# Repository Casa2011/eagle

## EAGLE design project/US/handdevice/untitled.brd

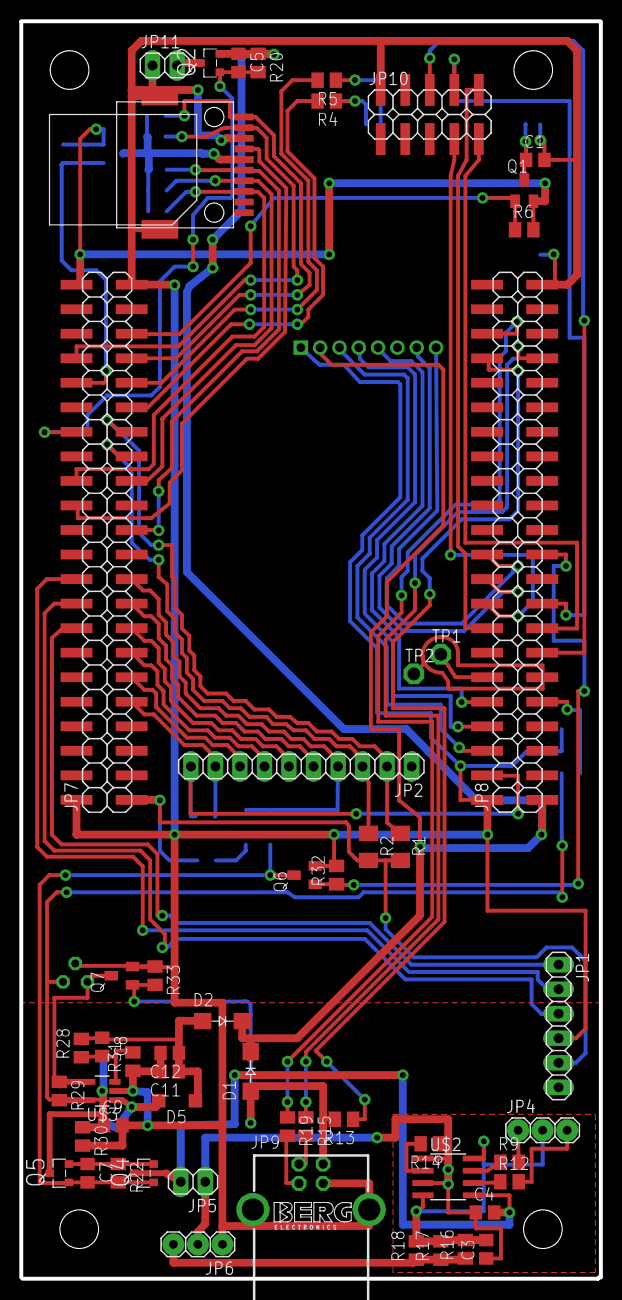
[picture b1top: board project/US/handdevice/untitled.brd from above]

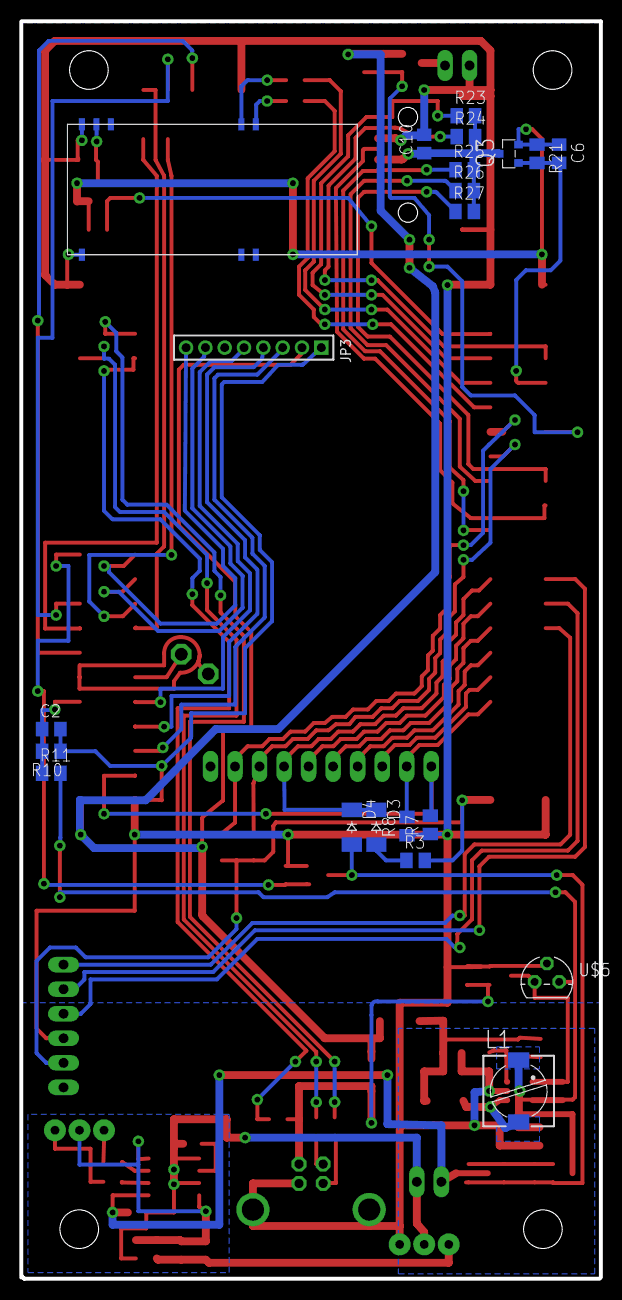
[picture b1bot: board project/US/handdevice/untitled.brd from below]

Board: 2 copper layers, 60.0 x 130.2 mm, 76 parts (21 on the bottom side), 68 nets.

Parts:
C1, C3, C9, C10, C11, C12: 10u; C0805
C2, C5, C6, C7: 100n; C0805
C4: 1u; C0805
C8: 200p; C0805
D1, D2: SS16; SMA-DO214AC
D3, D4: 1n4007; SOD-123_MINI-SMA
D5: SS14; SOD123
JP1: realtime_clock; 1X06
JP2: keyboard; 1X10
JP3: amplifier_control; 1X08M
JP4: charge_slot; 1X03
JP5: battery; 1X02
JP6: chrg; 1X03
JP7: left_cpu; 2X22SMD
JP8: right_cpu; 2X22SMD
JP9: USB_B; PN61729-S
JP10: display_data; 2X05SMD
JP11: display_pwr; 1X02
JP12: MICRO_SD; MICRO_SD_EASY
L1: 6,8u; PIS2816
Q1: IRLMLl2244; SOT23
Q2, Q3, Q4, Q5: IRLMLl2244; MICRO3
Q6, Q7: 2N7002; SOT23
R1, R2: 100k; M1206
R3, R6, R20, R21, R22, R29, R30, R32, R33: 100k; M0805
R4, R5, R9, R12, R13: 1k; M0805
R7, R8, R10, R11: 10k; M0805
R14: 1.2k; M0805
R15, R19: 10; M0805
R16, R17, R18: 1; M0805
R23, R24, R25, R26, R27: 50k; M0805
R28: 82k; M0805
R31: 27k; M0805
TP1, TP2: TPPAD1-13; P1-13
U$1: BLUETOOTH
U$2: TP4056; SO08
U$3: LM2731; SOT23-5
U$5: UVLO; TO-92

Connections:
5V: C5.1, D1.K, D2.K, JP3.2, JP8.1, Q2.2, R20.1
ADC1: C2.1, JP8.9, R10.2, R11.1
ADC2: JP8.12, TP1.TP
AMP_CHANELL: JP3.7, JP8.20
AMP_CHARGE: JP3.3, JP8.6
AMP_MUTE: JP3.8, JP8.22
AMP_OK: JP3.5, JP8.10
AMP_ON: JP3.4, JP8.8
A_GND: JP8.11, TP2.TP
BT_RUN: JP7.39, Q1.1, R6.1
CLK: JP7.26, JP12.CLK
CMD: JP7.23, JP12.CMD, R25.1
D0: JP7.38, JP12.DAT0, R24.1
D1: JP7.37, JP12.DAT1, R23.1
D2: JP7.28, JP12.DAT2, R27.1
D3: JP7.27, JP12.DAT3, R26.1
DC/DC_5V: C8.1, C11.1, C12.1, D2.A, D5.C, R28.2
DISPLAY_CS: JP8.16, JP10.10
DISPLAY_INT: JP8.13, JP10.6
DISPLAY_MISO: JP8.18, JP10.7
DISPLAY_MOSI: JP8.17, JP10.8
DISPLAY_SCK: JP8.15, JP10.9
DISP_ON: C5.2, JP7.32, Q2.1, R20.2
DM: JP8.37, R15.1
DP: JP8.40, R19.1
GND: C1.2, C2.2, C9.2, C10.2, C11.2, C12.2, JP1.4, JP3.1, JP6.1, JP7.2, JP7.43, JP8.2, JP8.43, JP9.4, JP9.S1, JP9.S2, JP10.2, JP11.1, JP12.G1, JP12.G2, JP12.GND, Q6.2, Q7.2, R7.1, R8.1, R10.1, R30.2, R31.1, R32.2, R33.1, U$1.GND, U$1.GND2, U$3.2, U$5.GND
K1: JP2.5, JP7.17
K2: JP2.6, JP7.15
K3: JP2.7, JP7.13
K4: JP2.8, JP7.11
K5: JP2.9, JP7.9, R8.2
K6: JP2.10, JP8.4, R7.2
LIPOL: C9.1, L1.1, Q5.3, R11.2, R29.2, R30.1, U$3.5, U$5.VIN
unnamed: R4.1, U$1.TX
unnamed: R5.1, U$1.RX
unnamed: C7.1, Q4.2, Q5.2, R22.1
unnamed: JP11.2, Q2.3
unnamed: JP6.3, R16.1, R17.1, R18.1
unnamed: C1.1, Q1.3, U$1.3V3
unnamed: R14.2, U$2.2
unnamed: C8.2, R28.1, R31.2, U$3.3
unnamed: C4.2, JP5.2, Q4.3, U$2.5
unnamed: D5.A, L1.2, U$3.1
unnamed: JP9.2, R15.2
unnamed: R9.1, U$2.7
unnamed: D3.A, R3.1
unnamed: R12.1, U$2.6
unnamed: Q7.3, R29.1, U$3.4, U$5.VOUT
unnamed: JP4.1, R9.2
unnamed: JP4.3, R12.2
unnamed: C3.1, C4.1, JP5.1, JP6.2, R14.1, U$2.1, U$2.3
unnamed: C3.2, JP4.2, R16.2, R17.2, R18.2, U$2.4, U$2.8
unnamed: JP9.3, R19.2
unnamed: C10.1, JP12.VCC, Q3.3, R23.2, R24.2, R25.2, R26.2, R27.2
PWR_BTN: C7.2, D4.A, Q4.1, Q5.1, Q6.3, R22.2
PWR_ON: JP8.21, Q6.1, R32.1
RTC_CLK: JP1.3, JP7.18
RTC_CS: JP1.1, JP7.16
RTC_IO: JP1.2, JP7.20
RX: JP7.33, R4.2
S1: JP2.2, JP7.31, R1.1
S2: JP2.3, JP7.29, R2.1
S3: D3.C, D4.C, JP2.4, JP7.19
SD_ON: C6.2, JP7.36, Q3.1, R21.2
TX: JP7.35, R5.2
USB_5V: D1.A, JP9.1, Q7.1, R13.2, R33.2
VBUS: JP8.38, R13.1
VCC: C6.1, JP1.5, JP7.1, JP7.44, Q1.2, Q3.2, R1.2, R2.2, R3.2, R6.2, R21.1

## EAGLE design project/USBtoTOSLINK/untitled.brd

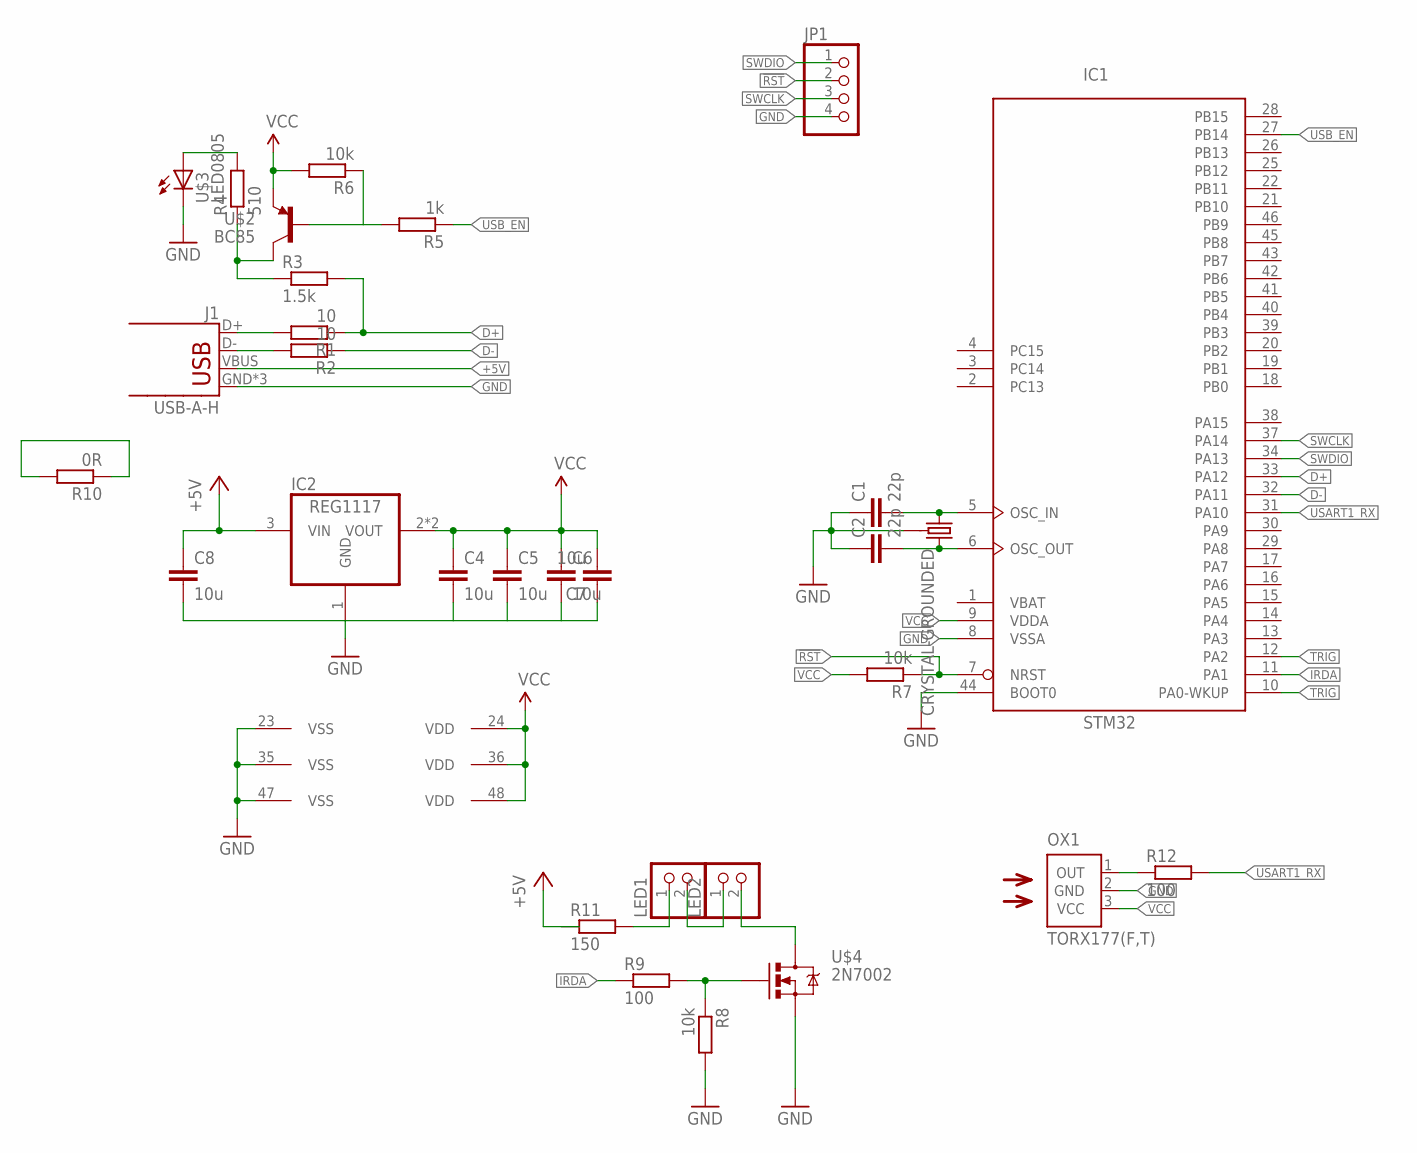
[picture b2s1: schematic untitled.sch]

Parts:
C1, C2: 22p; C0603
C4, C5, C6, C7, C8: 10u; C0805
IC1: STM32; LQFP48
IC2: REG1117; SOT223
J1: USB-A-H
JP1: PINHD-1X4; 1X04
LED1, LED2: PINHD-1X2; 1X02
OX1: TORX177(F,T); TORX
R1, R2: 10; 0603
R3: 1.5k; 0603
R4: 510; 0603
R5: 1k; 0603
R6, R7, R8: 10k; 0603
R9, R12: 100; 0603
R10: 0R; 0603
R11: 150; 0603
U$1: CRYSTAL-GROUNDED; CRYSTAL-SMD-5X3
U$2: BC85; SOT23
U$3: LED0805; 0805-LED
U$4: 2N7002; SOT23

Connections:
5VRLED: LED1.1, R11.2
!RST: IC1.7 (NRST), JP1.2, R7.1
+5V: C8.1, IC2.3 (VIN), J1.VBUS, R11.1
D+: IC1.33 (PA12), R1.1, R3.2
D-: IC1.32 (PA11), R2.1
GND: C1.1, C2.1, C4.2, C5.2, C6.2, C7.1, C8.2, IC1.8 (VSSA), IC1.23 (VSS), IC1.35 (VSS), IC1.44 (BOOT0), IC1.47 (VSS), IC2.1 (GND), J1.GND, J1.GND2 (GND), J1.GND3 (GND), JP1.4, OX1.2 (GND), R8.2, U$1.2 (3), U$1.4 (3), U$3.C, U$4.2 (S)
IRDA: IC1.11 (PA1), R9.1
unnamed: C2.2, IC1.6 (OSC_OUT), U$1.1 (2)
unnamed: C1.2, IC1.5 (OSC_IN), U$1.3 (1)
unnamed: R8.1, R9.2, U$4.1 (G)
unnamed: LED2.2, U$4.3 (D)
unnamed: J1.D-, R2.2
unnamed: J1.D+, R1.2
unnamed: LED1.2, LED2.1
unnamed: R3.1, R4.1, U$2.3 (C)
unnamed: R4.2, U$3.A
unnamed: R5.2, R6.1, U$2.1 (B)
SWCLK: IC1.37 (PA14), JP1.3
SWDIO: IC1.34 (PA13), JP1.1
TRIG: IC1.10 (PA0-WKUP), IC1.12 (PA2)
USART1_RX: IC1.31 (PA10), R12.2
USART1_RXR: OX1.1 (OUT), R12.1
USB_EN: IC1.27 (PB14), R5.1
VBAT: IC1.1 (VBAT)
VCC: C4.1, C5.1, C6.1, C7.2, IC1.9 (VDDA), IC1.24 (VDD), IC1.36 (VDD), IC1.48 (VDD), IC2.2 (VOUT), IC2.4 (VOUT), OX1.3 (VCC), R6.2, R7.2, R10.1, R10.2, U$2.2 (E)

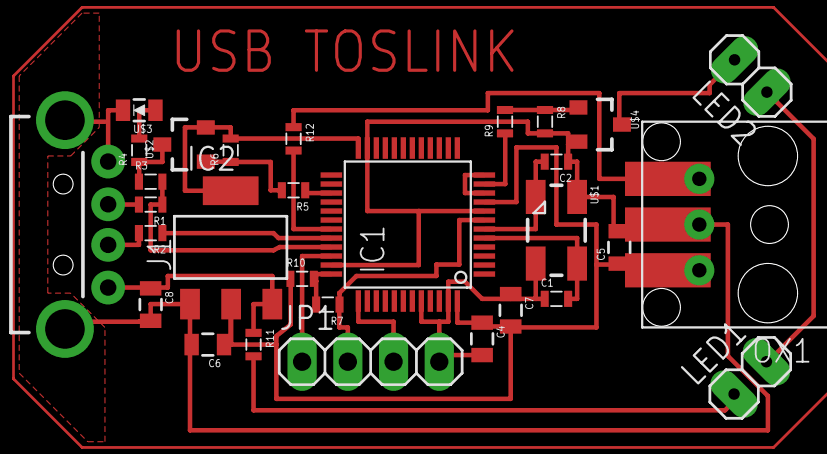
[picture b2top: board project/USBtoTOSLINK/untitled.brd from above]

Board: 2 copper layers, 30 parts (0 on the bottom side), 24 nets.

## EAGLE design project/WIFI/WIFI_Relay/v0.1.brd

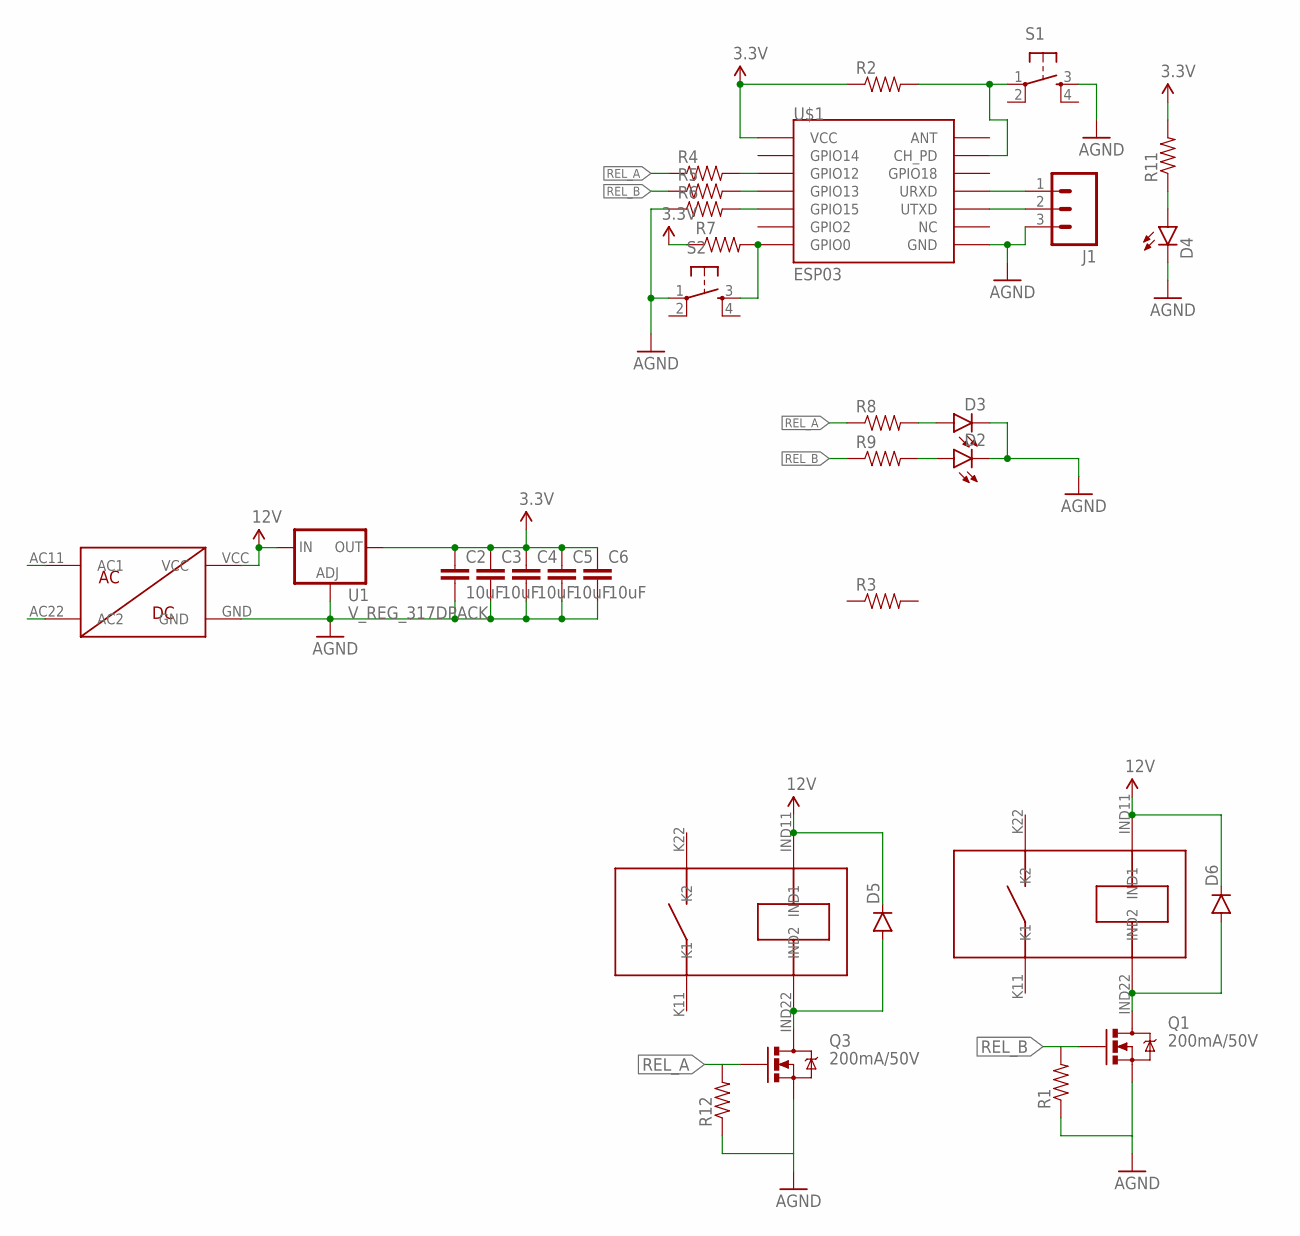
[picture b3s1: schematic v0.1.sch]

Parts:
C2, C3, C4, C5, C6: 10uF; 0603-CAP
D2, D3, D4: LED0603; LED-0603
D5, D6: DIODESOD123; SOD-123
J1: M03LONGPADS; 1X03_LONGPADS
Q1, Q3: 200mA/50V; SOT23-3
R1, R2, R3, R4, R5, R6, R7, R8, R9, R11, R12: RESISTOR0805-RES; 0805
S1, S2: TAC_SWITCHPTH; TACTILE-PTH
U1: V_REG_317DPACK; V-REG_DPACK
U$1: ESP03
U$8: ACDC12V350MA
U$9, U$10: 302WP

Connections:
3.3V: C2.1, C3.1, C4.1, C5.1, C6.1, R2.1, R7.1, R11.2, U1.4 (OUT), U$1.VCC
12V: D5.C, D6.C, U1.3 (IN), U$8.VCC, U$9.IND11 (IND1), U$10.IND11 (IND1)
AGND: C2.2, C3.2, C4.2, C5.2, C6.2, D2.C, D3.C, D4.C, J1.3, Q1.2 (S), Q3.2 (S), R1.1, R6.1, R12.1, S1.3, S2.1, U1.1 (ADJ), U$1.GND, U$8.GND
unnamed: J1.1, U$1.URXD
unnamed: J1.2, U$1.UTXD
unnamed: D5.A, Q3.3 (D), U$10.IND22 (IND2)
unnamed: R2.2, S1.1, U$1.CH_PD
unnamed: R4.2, U$1.GPIO12
unnamed: R5.2, U$1.GPIO13
unnamed: R6.2, U$1.GPIO15
unnamed: D3.A, R8.2
unnamed: D2.A, R9.2
unnamed: R7.2, S2.3, U$1.GPIO0
unnamed: D4.A, R11.1
unnamed: D6.A, Q1.3 (D), U$9.IND22 (IND2)
REL_A: Q3.1 (G), R4.1, R8.1, R12.2
REL_B: Q1.1 (G), R1.2, R5.1, R9.1

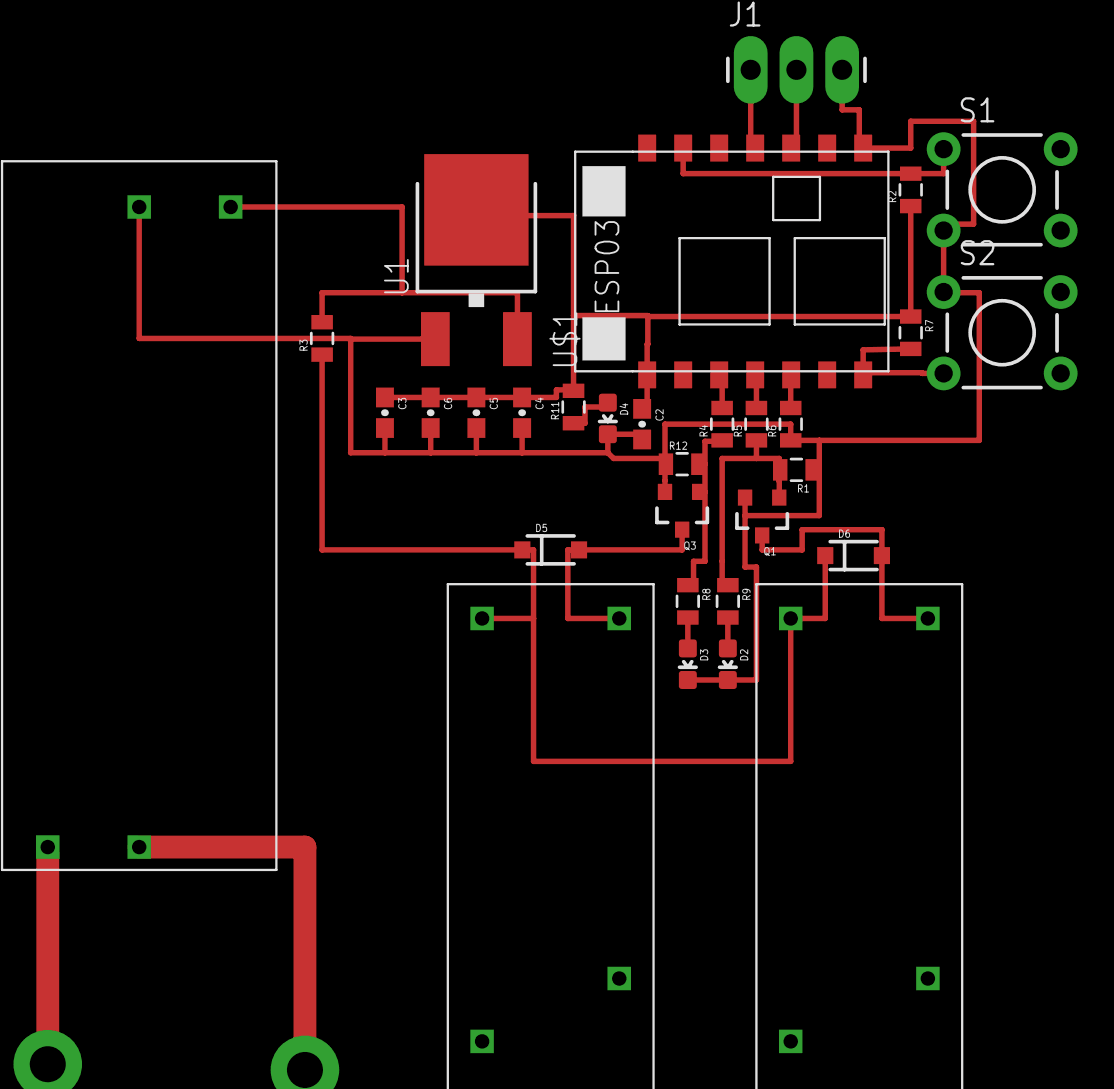
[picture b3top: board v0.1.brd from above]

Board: 2 copper layers, 31 parts (0 on the bottom side), 17 nets.

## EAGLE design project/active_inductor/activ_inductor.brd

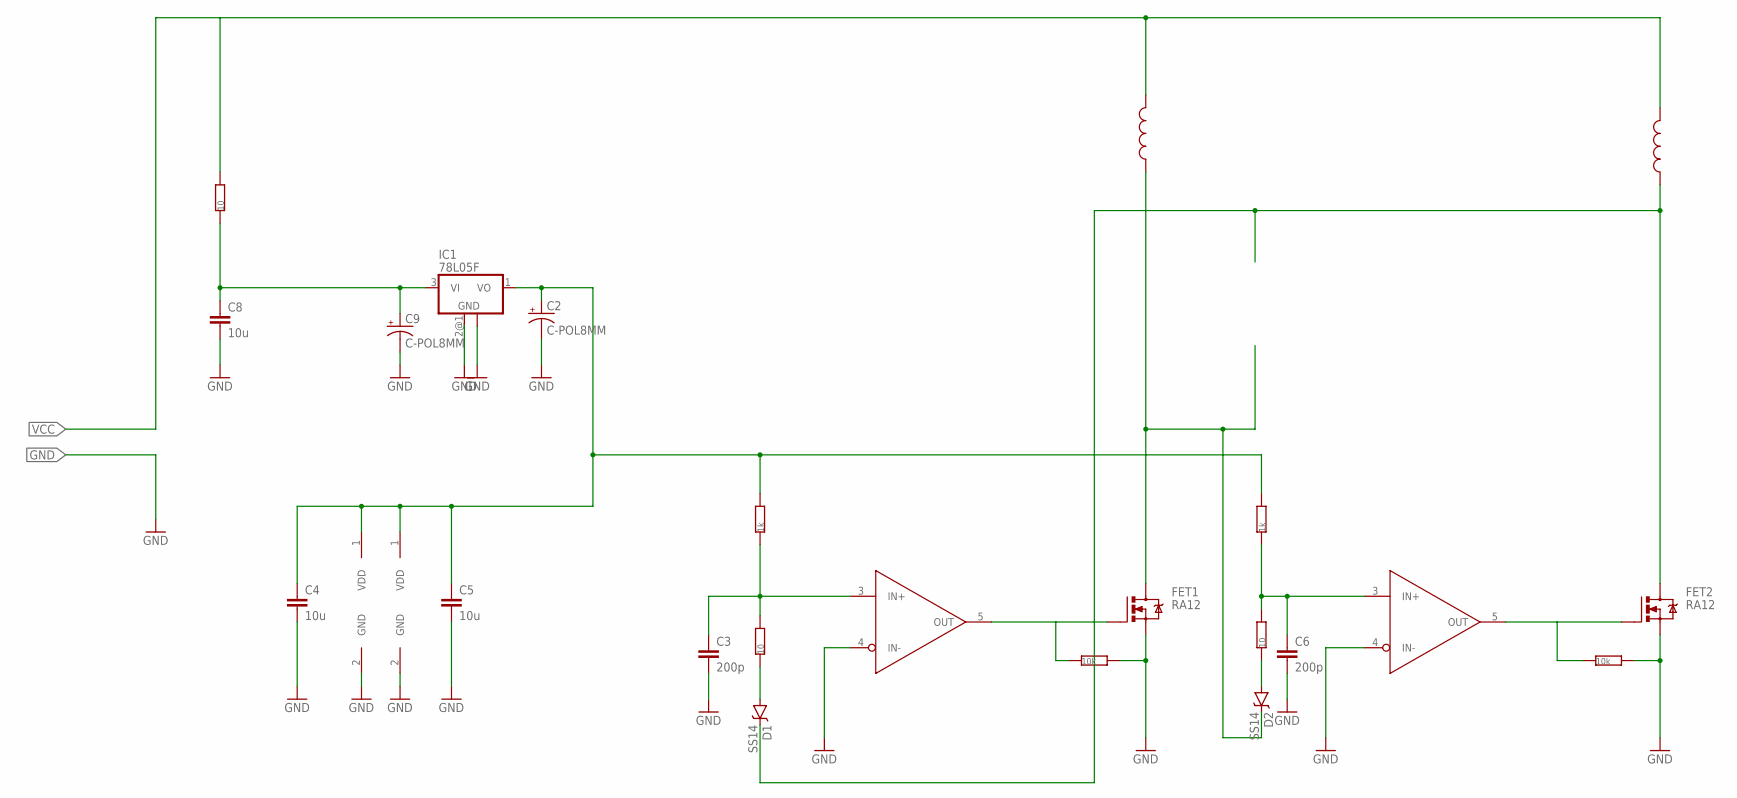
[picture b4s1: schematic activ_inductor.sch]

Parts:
C2, C9: C-POL8MM; PCAP8
C3, C6: 200p; C0805
C4, C5, C8: 10u; C0805
D1, D2: SS14; SMA-DIODE
FET1, FET2: RA12; POWERPAK_SO8
IC1: 78L05F; SOT89
R1, R2: 1k; R0805
R3, R4: 10k; R0805
R5: 10; R1206
R6, R7: 10; R0805
U$1, U$2: FAN3100; SOT23-5
U$4, U$5: INDUCTORRING_1; INDUCTOR

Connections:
GND: C2.P$2 (-), C3.2, C4.2, C5.2, C6.2, C8.2, C9.P$2 (-), FET1.1 (S), FET1.2 (S), FET1.3 (S), FET2.1 (S), FET2.2 (S), FET2.3 (S), IC1.2 (GND), IC1.2@1 (GND), R3.2, R4.2, U$1.2 (GND), U$1.4 (IN-), U$2.2 (GND), U$2.4 (IN-)
unnamed: D2.A, R6.1
unnamed: FET2.4 (G), R4.1, U$2.5 (OUT)
unnamed: D1.A, R7.1
unnamed: C3.1, R1.1, R7.2, U$1.3 (IN+)
unnamed: C6.1, R2.1, R6.2, U$2.3 (IN+)
unnamed: C8.1, C9.P$1 (+), IC1.3 (VI), R5.1
unnamed: C2.P$1 (+), C4.1, C5.1, IC1.1 (VO), R1.2, R2.2, U$1.1 (VDD), U$2.1 (VDD)
unnamed: FET1.4 (G), R3.1, U$1.5 (OUT)
PHA: D2.C, FET1.5 (D), FET1.6 (D), FET1.7 (D), FET1.8 (D), FET1.P$1 (D), U$5.1
PHB: D1.C, FET2.5 (D), FET2.6 (D), FET2.7 (D), FET2.8 (D), FET2.P$1 (D), U$4.1
VCC: R5.2, U$4.2, U$5.2

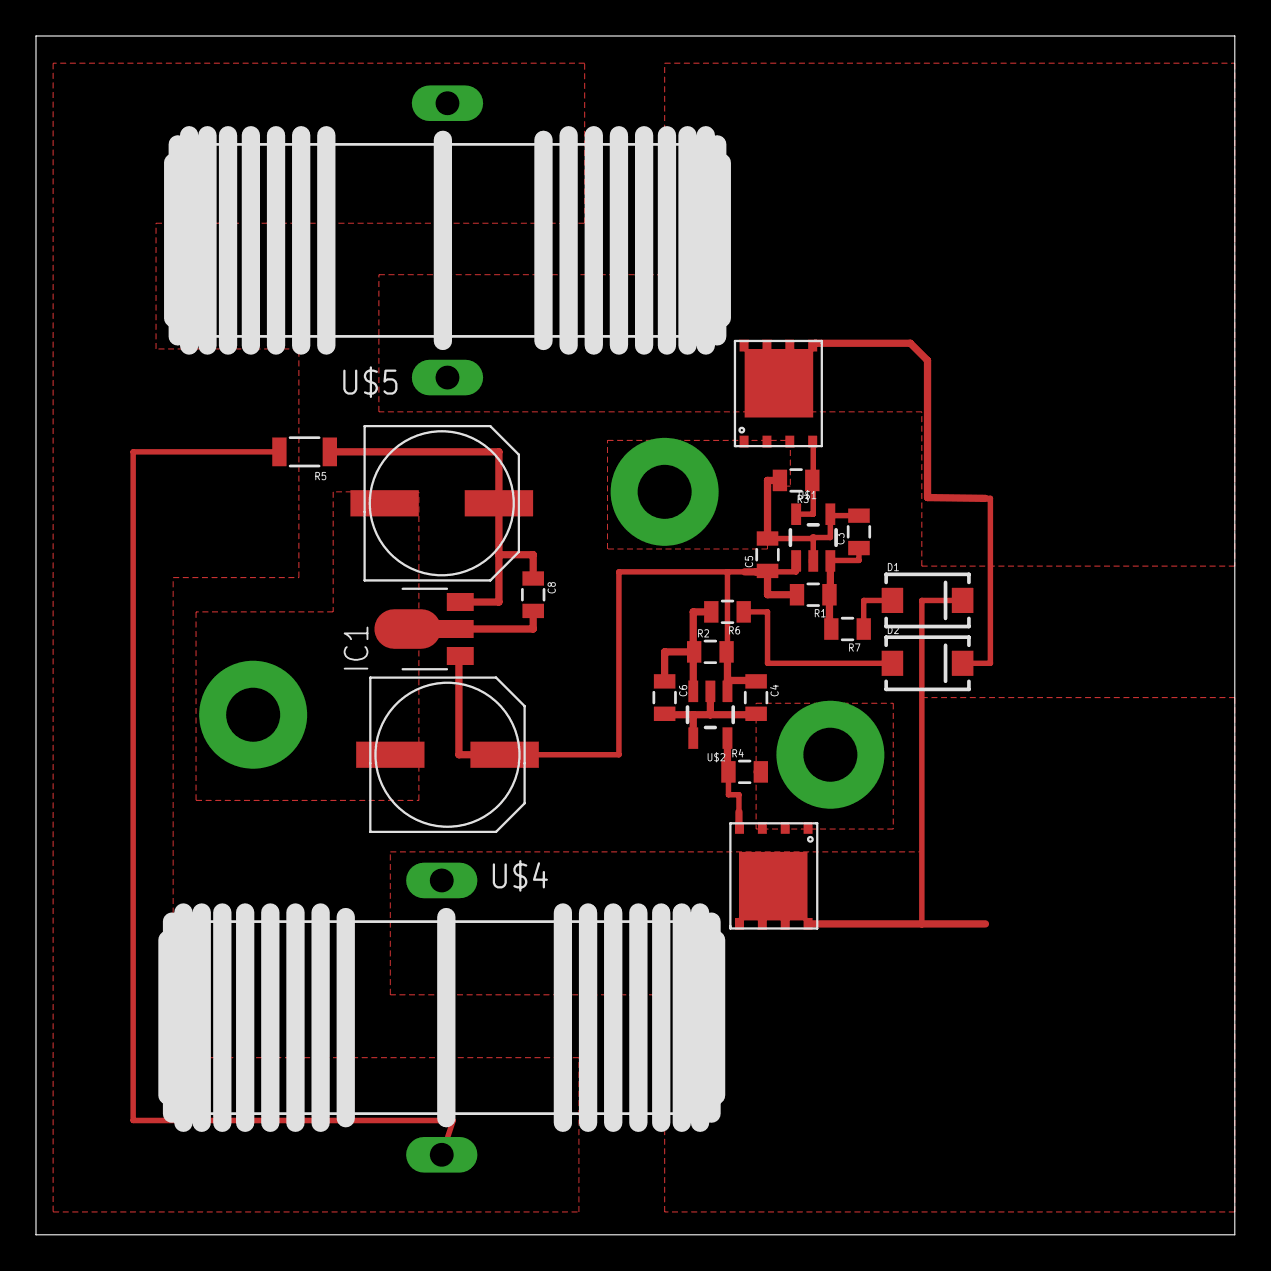
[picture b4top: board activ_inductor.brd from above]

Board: 2 copper layers, 66.6 x 66.6 mm, 23 parts (0 on the bottom side), 12 nets.

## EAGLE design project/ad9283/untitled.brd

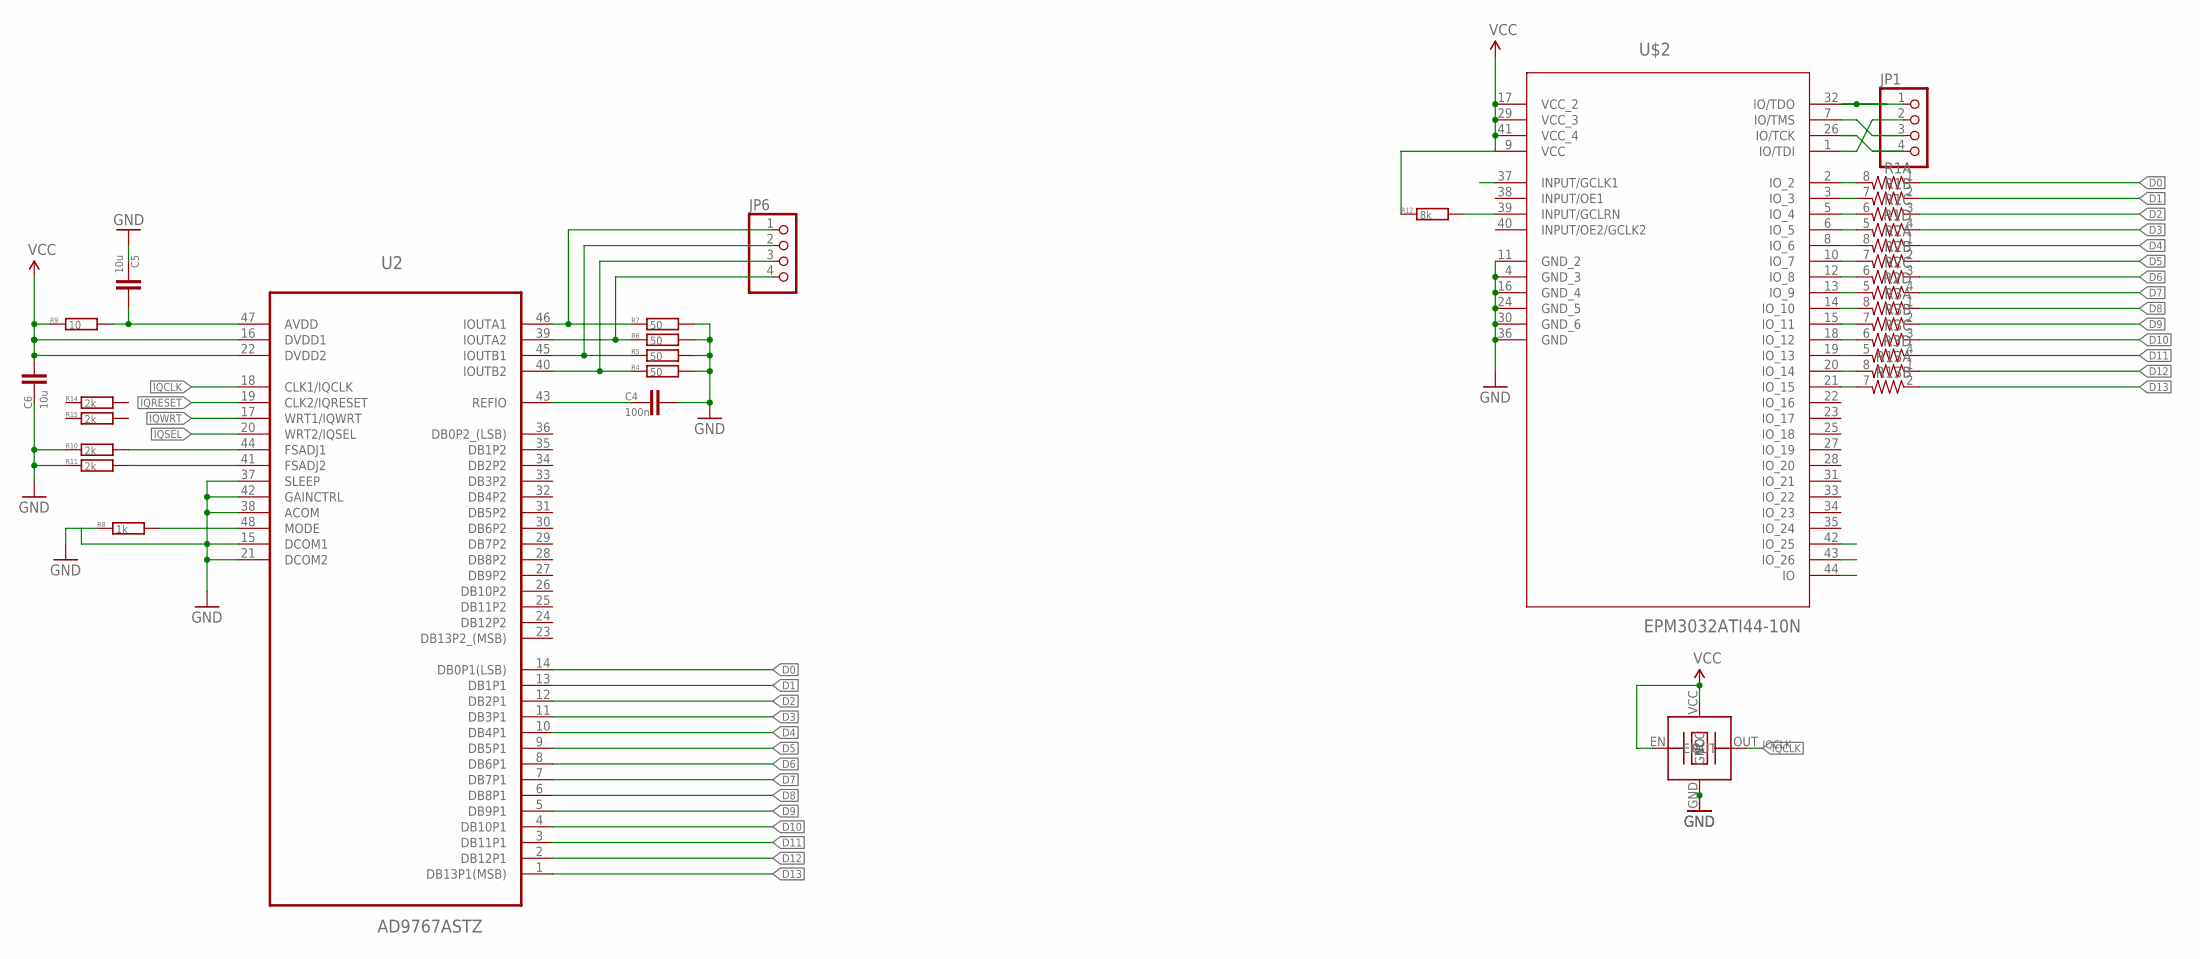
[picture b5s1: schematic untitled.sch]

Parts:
C4: 100n; C0805
C5, C6: 10u; C0805
JP1, JP6: PINHD-1X4; 1X04
R1, R2, R3, R13: RESISTOR-ARRAY0603-ARV; 0603-ARV
R4, R5, R6, R7: 50; R0805
R8: 1k; R0805
R9: 10; R0805
R10, R11, R14, R15: 2k; R0805
R12: 8k; R0805
U2: AD9767ASTZ; QFP50P900X900X160-48N
U$2: EPM3032ATI44-10N; QFP80P1200X1200X120-44N
U$3: TXC-BA; 7X5

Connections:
!OUT1: JP6.2, R5.1, U2.45 (IOUTB1)
!OUT2: JP6.4, R6.1, U2.39 (IOUTA2)
D0: R1.1, U2.14 (DB0P1(LSB))
D1: R1.2 (1), U2.13 (DB1P1)
D2: R1.3 (1), U2.12 (DB2P1)
D3: R1.4 (1), U2.11 (DB3P1)
D4: R2.1, U2.10 (DB4P1)
D5: R2.2 (1), U2.9 (DB5P1)
D6: R2.3 (1), U2.8 (DB6P1)
D7: R2.4 (1), U2.7 (DB7P1)
D8: R3.1, U2.6 (DB8P1)
D9: R3.2 (1), U2.5 (DB9P1)
D10: R3.3 (1), U2.4 (DB10P1)
D11: R3.4 (1), U2.3 (DB11P1)
D12: R13.1, U2.2 (DB12P1)
D13: R13.2 (1), U2.1 (DB13P1(MSB))
GND: C4.1, C5.2, C6.2, R4.2, R5.2, R6.2, R7.2, R8.1, R10.1, R11.1, U2.15 (DCOM1), U2.21 (DCOM2), U2.37 (SLEEP), U2.38 (ACOM), U2.42 (GAINCTRL), U$2.4 (GND_3), U$2.11 (GND_2), U$2.16 (GND_4), U$2.24 (GND_5), U$2.30 (GND_6), U$2.36 (GND), U$3.GND
IQCLK: U2.18 (CLK1/IQCLK), U$2.37 (INPUT/GCLK1), U$3.OUT
IQRESET: U2.19 (CLK2/IQRESET), U$2.43 (IO_26)
IQSEL: U2.20 (WRT2/IQSEL), U$2.42 (IO_25)
IQWRT: U2.17 (WRT1/IQWRT), U$2.44 (IO)
unnamed: C5.1, R9.2, U2.47 (AVDD)
unnamed: R8.2, U2.48 (MODE)
unnamed: R12.2, U$2.39 (INPUT/GCLRN)
unnamed: R10.2, U2.44 (FSADJ1)
unnamed: JP1.1, U$2.32 (IO/TDO)
unnamed: JP1.3, U$2.7 (IO/TMS)
unnamed: JP1.2, U$2.1 (IO/TDI)
unnamed: JP1.4, U$2.26 (IO/TCK)
unnamed: R11.2, U2.41 (FSADJ2)
unnamed: R1.8 (2), U$2.2 (IO_2)
unnamed: R1.7 (2), U$2.3 (IO_3)
unnamed: C4.2, U2.43 (REFIO)
unnamed: R1.6 (2), U$2.5 (IO_4)
unnamed: R1.5 (2), U$2.6 (IO_5)
unnamed: R2.8 (2), U$2.8 (IO_6)
unnamed: R2.7 (2), U$2.10 (IO_7)
unnamed: R2.6 (2), U$2.12 (IO_8)
unnamed: R2.5 (2), U$2.13 (IO_9)
unnamed: R3.8 (2), U$2.14 (IO_10)
unnamed: R3.7 (2), U$2.15 (IO_11)
unnamed: R3.6 (2), U$2.18 (IO_12)
unnamed: R3.5 (2), U$2.19 (IO_13)
unnamed: R13.8 (2), U$2.20 (IO_14)
unnamed: R13.7 (2), U$2.21 (IO_15)
OUT1: JP6.1, R7.1, U2.46 (IOUTA1)
OUT2: JP6.3, R4.1, U2.40 (IOUTB2)
VCC: C6.1, R9.1, R12.1, U2.16 (DVDD1), U2.22 (DVDD2), U$2.9 (VCC), U$2.17 (VCC_2), U$2.29 (VCC_3), U$2.41 (VCC_4), U$3.EN, U$3.VCC

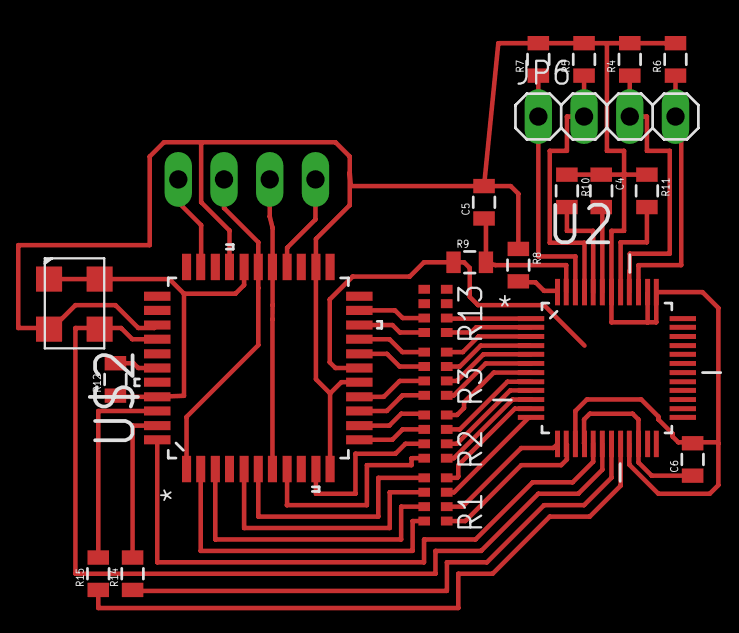
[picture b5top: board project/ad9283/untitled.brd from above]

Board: 2 copper layers, 23 parts (1 on the bottom side), 48 nets.

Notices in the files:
parts and their libraries:
SparkFun-FreqCtrl: Licensing: Creative Commons ShareAlike 4.0 International - https://creativecommons.org/licenses/by-sa/4.0
